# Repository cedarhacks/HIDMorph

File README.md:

# HIDMorph

**HIDMorph** is a programmable USB HID host/device translator built on a dual-MCU architecture (ESP32-S3 + RP2040).  
It enables real-time translation, remapping, and transformation of USB HID inputs (keyboards, mice, controllers) without requiring firmware recompilation.

The system is designed as an embedded product, combining real-time firmware, USB protocol handling, and custom hardware.

---

## What HIDMorph Does

- Acts as a **USB HID host and USB HID device** simultaneously  
- Translates HID inputs (e.g. keyboard → joystick, macros, custom mappings) in real time  
- Supports **runtime-configurable behavior** via a Lua scripting layer  
- Designed for low-latency, deterministic input handling  
- Runs entirely on-device (no PC software required after setup)

---

## Architecture Overview

HIDMorph uses a **dual-MCU design** to cleanly separate USB responsibilities:

- **RP2040**
  - USB Host stack
  - Enumerates and reads input HID devices
  - Handles timing-sensitive USB host transactions

- **ESP32-S3**
  - USB Device stack (HID output)
  - Runs FreeRTOS-based application logic
  - Executes Lua scripts for dynamic input translation
  - Manages on-device filesystem and configuration

Communication between MCUs is handled over a dedicated internal interface designed for low latency and robustness.

*(Architecture diagram coming soon)*

---

## Firmware

- **RTOS:** FreeRTOS  
- **USB Stack:** TinyUSB  
- **Languages:** C/C++, Lua  
- **Features:**
  - USB HID descriptor management
  - Class handling for common HID devices
  - Scriptable runtime for input translation
  - Fault handling and recovery paths for USB disconnects

---

## Hardware

- Custom PCB designed in KiCad  
- Dual-MCU architecture (ESP32-S3 + RP2040)  
- USB host and device interfaces  
- Designed for iterative hardware bring-up and revision

*(Schematics, PCB renders, and photos will be added as the design stabilizes)*

---

## Project Status

HIDMorph is under **active development**.

Completed:
- Core dual-MCU architecture
- USB host/device communication path
- Base firmware framework
- Lua runtime integration
- Initial PCB revisions and bring-up

In progress:
- Expanded HID device support
- Improved scripting APIs
- Documentation and examples
- Enclosure refinement

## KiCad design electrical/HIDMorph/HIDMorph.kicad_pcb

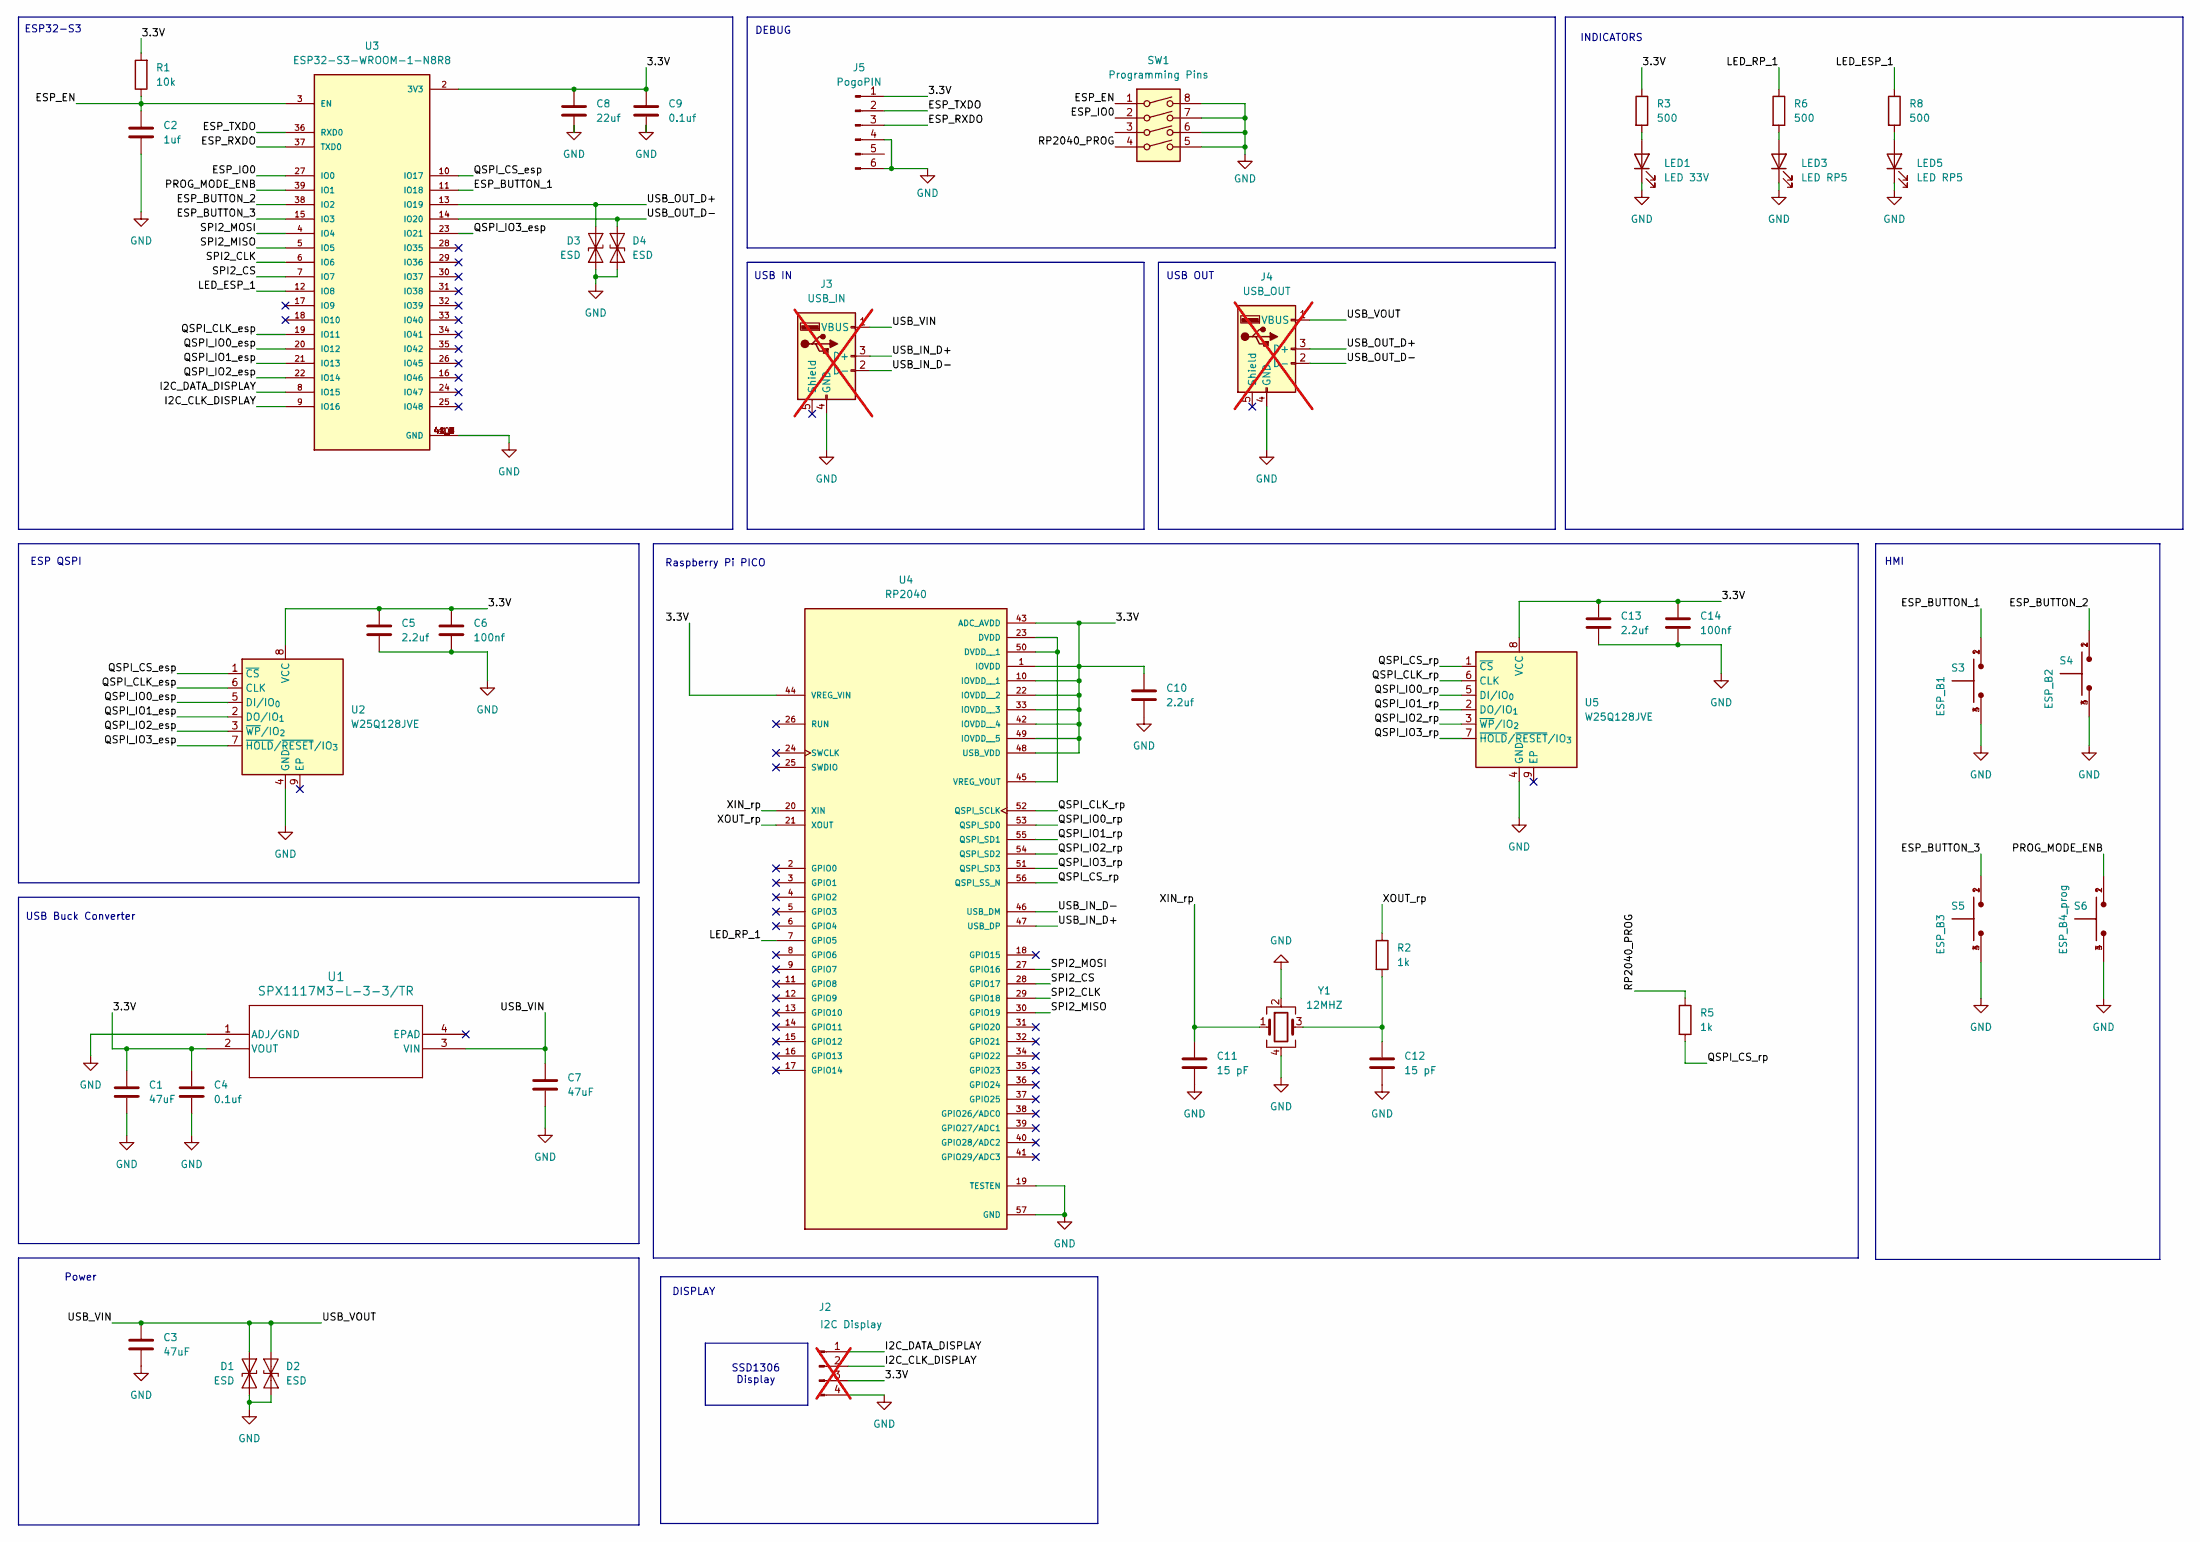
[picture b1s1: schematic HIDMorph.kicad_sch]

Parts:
C1, C3, C7: 47uF; C_0603_1608Metric; LCSC Part C140782
C2: 1uf; C_0603_1608Metric; LCSC Part C5189821
C4, C9: 0.1uf; C_0603_1608Metric; LCSC Part C14663
C5, C10, C13: 2.2uf; C_0603_1608Metric; LCSC Part C5189830
C6, C14: 100nf; C_0603_1608Metric; LCSC Part C5189821
C8: 22uf; C_0603_1608Metric; LCSC Part C48579267
C11, C12: 15 pF; C_0603_1608Metric; LCSC Part C107037
D1, D2, D3, D4: ESD; D_SOD-523; LCSC Part C5199159
J2: I2C Display; PinHeader_1x04_P2.54mm_Vertical; not fitted
J3: USB_IN; USBA_Female; not fitted
J4: USB_OUT; PinHeader_1x05_P2.54mm_Vertical; not fitted
J5: PogoPIN; pogo_pin_2.54mm
LED1: LED 33V; LED_0603_1608Metric; LCSC Part C965807
LED3, LED5: LED RP5; LED_0603_1608Metric; LCSC Part C965807
R1: 10k; R_0603_1608Metric; LCSC Part C98220
R2, R5: 1k; R_0603_1608Metric; LCSC Part C22548
R3, R6, R8: 500; R_0603_1608Metric; LCSC Part C860931
S3: ESP_B1; SW-SMD_4P-L4.5-W4.5-P3.00-LS6.8; LCSC Part C2837554
S4: ESP_B2; SW-SMD_4P-L4.5-W4.5-P3.00-LS6.8; LCSC Part C2837554
S5: ESP_B3; SW-SMD_4P-L4.5-W4.5-P3.00-LS6.8; LCSC Part C2837554
S6: ESP_B4_prog; SW-SMD_4P-L4.5-W4.5-P3.00-LS6.8; LCSC Part C2837554
SW1: Programming Pins; SW_DIP_219-4
U1: SPX1117M3-L-3-3/TR; SOT-223; LCSC Part C6862
U2, U5: W25Q128JVE; WSON-8-1EP_8x6mm_P1.27mm_EP3.4x4.3mm; LCSC Part C401662
U3: ESP32-S3-WROOM-1-N8R8; ESP32-S3-WROOM-1; LCSC Part C2913201
U4: RP2040; rp2040; PARTREV 2.2; LCSC Part C2040
Y1: 12MHZ; Crystal_SMD_3225-4Pin_3.2x2.5mm; LCSC Part C9002

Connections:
/3.3V: C1.1, C4.1, C5.1, C6.1, C8.1, C9.1, C10.1, C13.1, C14.1, J2.3, J5.1, R1.2, R3.1, U1.2 (VOUT), U2.8 (VCC), U3.2 (3V3), U4.1 (IOVDD), U4.10 (IOVDD__1), U4.22 (IOVDD__2), U4.33 (IOVDD__3), U4.42 (IOVDD__4), U4.43 (ADC_AVDD), U4.44 (VREG_VIN), U4.48 (USB_VDD), U4.49 (IOVDD__5), U5.8 (VCC)
/ESP_BUTTON_1: S3.1, S3.2, U3.11 (IO18)
/ESP_BUTTON_2: S4.1, S4.2, U3.38 (IO2)
/ESP_BUTTON_3: S5.1, S5.2, U3.15 (IO3)
/ESP_EN: C2.1, R1.1, SW1.1, U3.3 (EN)
/ESP_IO0: SW1.2, U3.27 (IO0)
/ESP_RXDO: J5.3, U3.37 (TXD0)
/ESP_TXDO: J5.2, U3.36 (RXD0)
/I2C_CLK_DISPLAY: J2.2, U3.9 (IO16)
/I2C_DATA_DISPLAY: J2.1, U3.8 (IO15)
/LED_ESP_1: R8.1, U3.12 (IO8)
/LED_RP_1: R6.1, U4.7 (GPIO5)
/PROG_MODE_ENB: S6.1, S6.2, U3.39 (IO1)
/QSPI_CLK_esp: U2.6 (CLK), U3.19 (IO11)
/QSPI_CLK_rp: U4.52 (QSPI_SCLK), U5.6 (CLK)
/QSPI_CS_esp: U2.1 (~CS), U3.10 (IO17)
/QSPI_CS_rp: R5.2, U4.56 (QSPI_SS_N), U5.1 (~CS)
/QSPI_IO0_esp: U2.5 (DI/IO_{0}), U3.20 (IO12)
/QSPI_IO0_rp: U4.53 (QSPI_SD0), U5.5 (DI/IO_{0})
/QSPI_IO1_esp: U2.2 (DO/IO_{1}), U3.21 (IO13)
/QSPI_IO1_rp: U4.55 (QSPI_SD1), U5.2 (DO/IO_{1})
/QSPI_IO2_esp: U2.3 (~WP/IO_{2}), U3.22 (IO14)
/QSPI_IO2_rp: U4.54 (QSPI_SD2), U5.3 (~WP/IO_{2})
/QSPI_IO3_esp: U2.7 (~HOLD/~RESET/IO_{3}), U3.23 (IO21)
/QSPI_IO3_rp: U4.51 (QSPI_SD3), U5.7 (~HOLD/~RESET/IO_{3})
/RP2040_PROG: R5.1, SW1.4
/SPI2_CLK: U3.6 (IO6), U4.29 (GPIO18)
/SPI2_CS: U3.7 (IO7), U4.28 (GPIO17)
/SPI2_MISO: U3.5 (IO5), U4.30 (GPIO19)
/SPI2_MOSI: U3.4 (IO4), U4.27 (GPIO16)
/USB_IN_D+: J3.3 (D+), U4.47 (USB_DP)
/USB_IN_D-: J3.2 (D-), U4.46 (USB_DM)
/USB_OUT_D+: D3.1 (A1), J4.3 (D+), U3.13 (IO19)
/USB_OUT_D-: D4.2 (A2), J4.2 (D-), U3.14 (IO20)
/USB_VIN: C3.1, C7.1, D1.1 (A1), D2.2 (A2), J3.1 (VBUS), J4.1 (VBUS), U1.3 (VIN)
/XIN_rp: C11.1, U4.20 (XIN), Y1.1
/XOUT_rp: R2.1, U4.21 (XOUT)
GND: C1.2, C2.2, C3.2, C4.2, C5.2, C6.2, C7.2, C8.2, C9.2, C10.2, C11.2, C12.2, C13.2, C14.2, D1.2 (A2), D2.1 (A1), D3.2 (A2), D4.1 (A1), J2.4, J3.4 (GND), J4.4 (GND), J5.4, J5.6, LED1.1 (K), LED3.1 (K), LED5.1 (K), S3.3, S3.4, S4.3, S4.4, S5.3, S5.4, S6.3, S6.4, SW1.5, SW1.6, SW1.7, SW1.8, U1.1 (ADJ/GND), U2.4 (GND), U3.1 (GND), U3.40 (GND), U3.41_1 (GND), U3.41_2 (GND), U3.41_3 (GND), U3.41_4 (GND), U3.41_5 (GND), U3.41_6 (GND), U3.41_7 (GND), U3.41_8 (GND), U3.41_9 (GND), U4.19 (TESTEN), U4.57 (GND), U5.4 (GND), Y1.2, Y1.4
unnamed: C12.1, R2.2, Y1.3
unnamed: LED1.2 (A), R3.2
unnamed: LED3.2 (A), R6.2
unnamed: LED5.2 (A), R8.2
unnamed: U4.23 (DVDD), U4.45 (VREG_VOUT), U4.50 (DVDD__1)

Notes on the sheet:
INDICATORS
USB IN
DISPLAY
ESP QSPI
USB Buck Converter
Power
USB OUT
Raspberry Pi PICO
ESP32-S3
HMI
SSD1306 Display
DEBUG

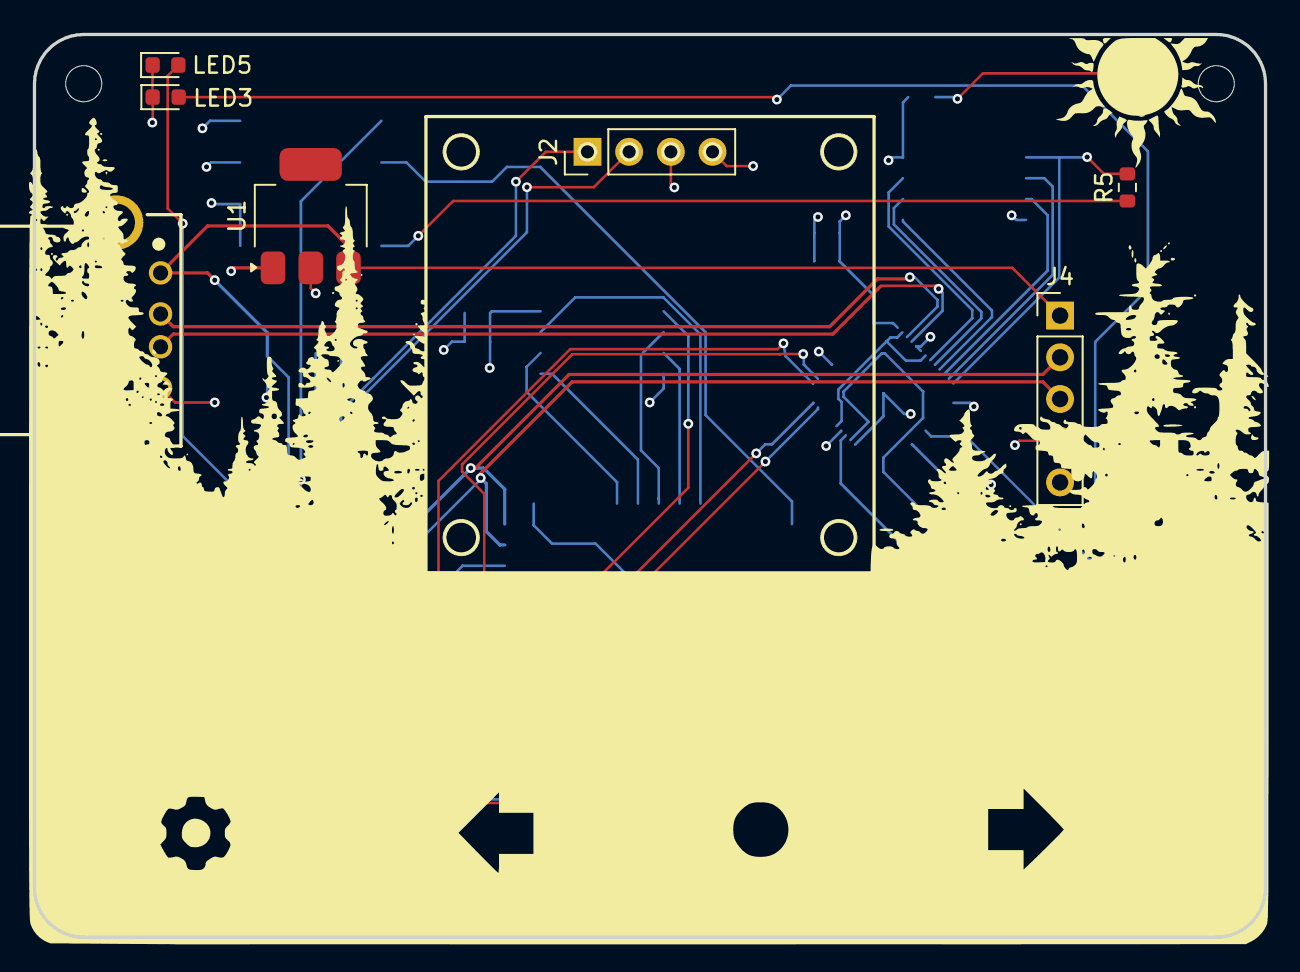
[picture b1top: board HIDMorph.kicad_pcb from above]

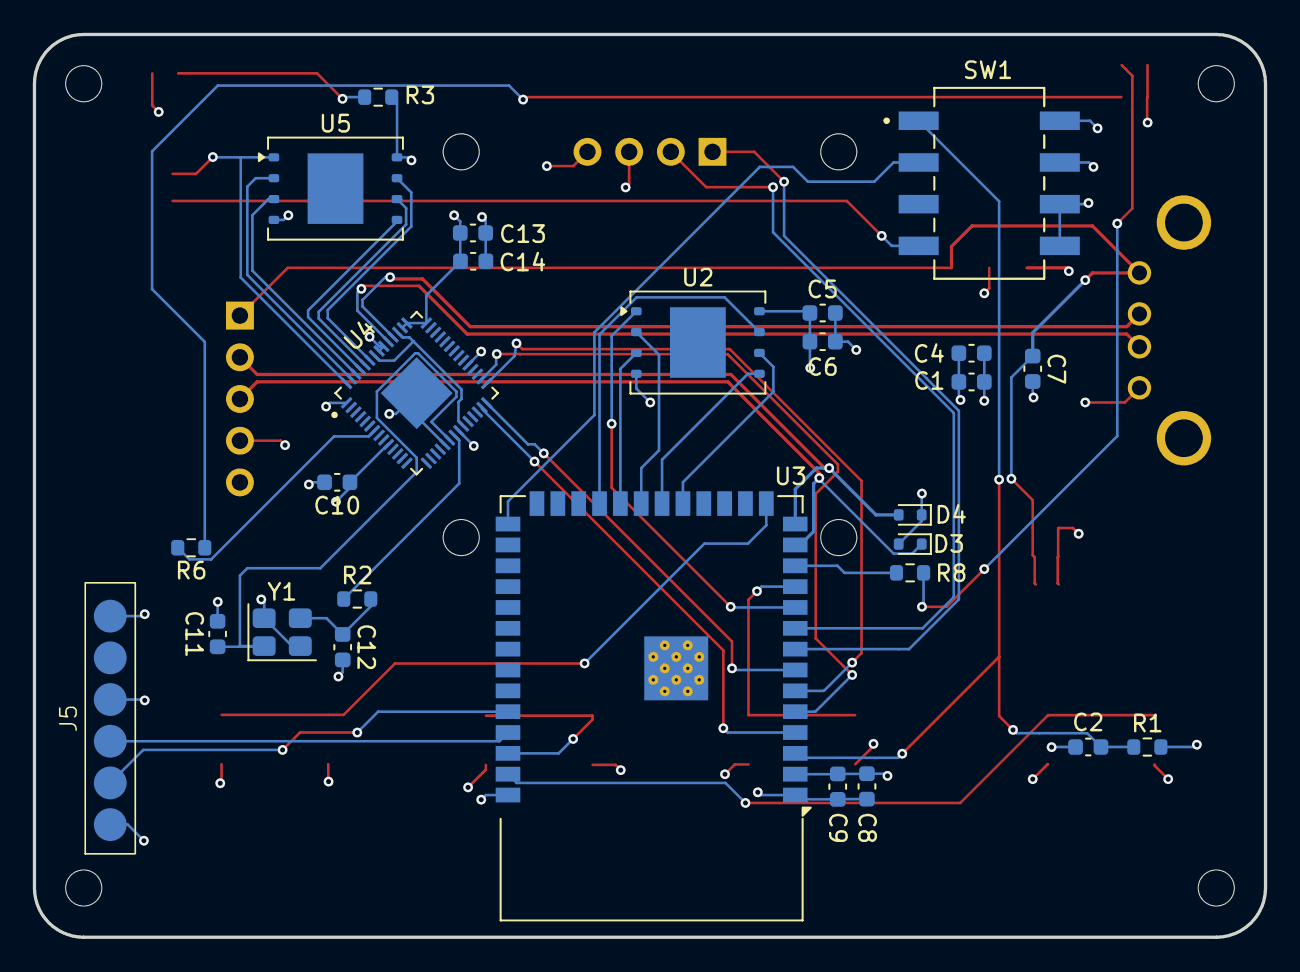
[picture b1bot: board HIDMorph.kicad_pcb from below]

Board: 4 copper layers, 75.0 x 55.0 mm, 42 parts (27 on the bottom side), 43 nets.

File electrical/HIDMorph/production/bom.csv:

Designator,Footprint,Quantity,Value,LCSC Part #
"_8, _7, _6, _5, _4, _3, _2, ",,8,,
"C1, C3, C7",0603,3,47uF,C140782
"C10, C13, C5",0603,3,2.2uf,C5189830
"C11, C12",0603,2,15 pF,C107037
"C14, C6",0603,2,100nf,C5189821
C2,0603,1,1uf,C5189821
"C4, C9",0603,2,0.1uf,C14663
C8,0603,1,22uf,C48579267
"D1, D2, D3, D4",D_SOD-523,4,ESD,C5199159
J5,pogo_pin_2.54mm,1,PogoPIN,
LED1,0603,1,LED 33V,C965807
"LED3, LED5",0603,2,LED RP5,C965807
R1,0603,1,10k,C98220
"R2, R5",0603,2,1k,C22548
"R3, R6, R8",0603,3,500,C860931
S3,SW-SMD_4P-L4.5-W4.5-P3.00-LS6.8,1,ESP_B1,C2837554
S4,SW-SMD_4P-L4.5-W4.5-P3.00-LS6.8,1,ESP_B2,C2837554
S5,SW-SMD_4P-L4.5-W4.5-P3.00-LS6.8,1,ESP_B3,C2837554
S6,SW-SMD_4P-L4.5-W4.5-P3.00-LS6.8,1,ESP_B4_prog,C2837554
SW1,SW_DIP_219-4,1,Programming Pins,
U1,SOT-223,1,SPX1117M3-L-3-3/TR,C6862
"U2, U5",WSON-8-1EP_8x6mm_P1.27mm_EP3.4x4.3mm,2,W25Q128JVE,C401662
U3,ESP32-S3-WROOM-1,1,ESP32-S3-WROOM-1-N8R8,C2913201
U4,rp2040,1,RP2040,C2040
Y1,Crystal_SMD_3225-4Pin_3.2x2.5mm,1,12MHZ,C9002

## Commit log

2025-07-15 added V1 Files post fab
2025-07-17 tested V2
2025-07-17 started adding dns
2025-08-29 can't get embed to work
2025-09-01 working embed
2025-09-02 working server
2025-09-03 file structure cleanup, I was going insane
2025-09-03 Started work on flash chip filesystem
2025-09-05 flash chip is communicating
2025-09-06 mounting as fatfs with vfs and wear levelling
2025-09-06 combine init for vfs
2025-09-06 tiny usb enable, no compile
2025-09-09 removing old HID code, working on composite usb code now
2025-09-09 Made it work as a usb MSC device in programming mode
2025-09-10 working now as MSC and HID device selectively
2025-09-11 readme todos
2025-09-12 gpio programming mode
2025-09-14 readme
2025-09-17 modified schematic to reflect i2c screen, 3 new buttons and 1 new switch
2025-09-18 schematic update, pcb design rules and blank slate on pcb editor
2025-09-18 started work on V3
2025-09-19 more component placement, removed lots of debug and hmi
2025-09-19 first layout attempt, had to compromise on some SMD and shrink the header pins
2025-09-19 It ssems too small, I need some space for trace highways
2025-09-20 way happier with this layout
2025-09-20 only warnings left on DRC
2025-09-20 drc passed, added silkscreen
2025-09-20 working on fab
2025-09-20 V3 to fab
2025-09-23 Readme update
2025-10-01 working display, V3 tested
2025-10-05 schematics
2025-10-05 lua VM
2025-10-05 lua vm executing
2025-10-08 error check sometimes fails due to data4... im not sure
2025-10-08 started working gui task, but having memory issues. Needs some serious thought
2025-10-08 gui task shared
2025-10-09 just some testing
2025-10-09 something wrong is going on
2025-10-10 some image and animation for programming mode
2025-10-14 wrestling with lvgl
2025-10-15 Fixed pesky seg fault and made stack sizes more sensible
2025-10-15 gui code finally looking better. starting to dislike lvgl more. Need to remove /mnt from user facing gui. Input manager next
2025-10-16 display file name only
2025-10-17 input manager first pass
2025-10-17 next and prev buttons working
2025-10-17 maybe a bit more appealing
2025-11-03 some progress on the input logic
2025-11-07 long filenames
2025-11-08 Better without animations
2025-11-08 running lua task
2025-11-09 working mouse wiggle
2025-11-09 some renaming
2025-11-09 fixed bug exiting lua too soon
2025-11-09 mouse circile test
2025-11-12 made the event quees more general, added an input and output q
2025-11-12 keyboard input callback. Missing lots of keys needs work
2025-11-13 fixed bug missing keys. Increased spi rate to 20mhz. 40mhz should be possible. Maybe the signal is bad? scope it out
2025-11-13 issues with timing present
2025-11-14 working well with wasd
2025-11-14 started work on mouse input pipeline
2025-11-14 moving raw mouse events through, still need to trigger lua event from it
2025-11-15 hooked up mouse callback in lua
2025-11-15 tested file write, added an erase mode and some default directories
2025-11-15 fixed custom file open
2025-11-16 gui sync function as well as ability to modify text in run mode
2025-11-18 work on recording
2025-11-18 recording innacurate, but functional
2025-11-18 fixed bug with multi size mouse report. need to fix properly next time. Fix delays in mouse passthrough
2025-11-18 passthrough delay fixed, but recording still broken
2025-11-19 get time function in lua
2025-11-20 usb_flash prio
2025-11-20 need to add event queue output with timing
2025-11-22 first smash proof of concept
2025-11-25 debugging controllers
2025-12-03 starting to fix button mappings
2025-12-17 started working on v5
2025-12-17 perhaps good layout
2025-12-18 dip switch, more layout fixes
2025-12-18 passing DRC
2025-12-19 pre-production
2025-12-23 sent to fab
2025-12-23 changhed to 64 pixel height ssd1306
2025-12-24 changed gui to fit bigger screen a little
2026-01-06 cad files
2026-01-06 re-nameing to HIDMorph
2026-01-15 added assembly map and ibom
